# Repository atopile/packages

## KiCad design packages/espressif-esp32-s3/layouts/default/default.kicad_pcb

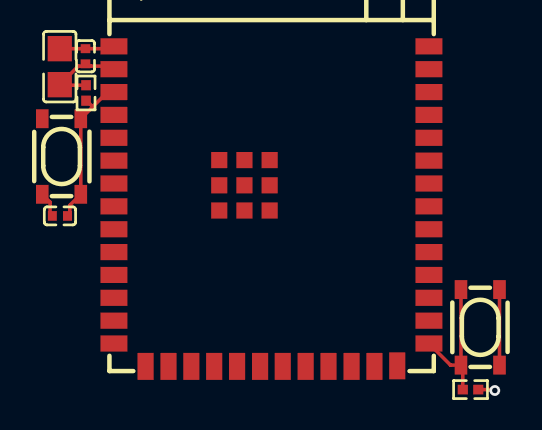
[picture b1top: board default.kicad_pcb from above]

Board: 2 copper layers, 8 parts (0 on the bottom side), 4 nets.

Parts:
C1: 10µF ±10%; C0805
C2: 100nF ±10%; C0402
C3: 1µF ±10%; C0402
R1, R2: 10kΩ ±1%; R0402
SW1, SW2: KEY-SMD_4P-L4.2-W3.2-P2.20-LS4.6
U1: WIRELM-SMD_ESP32-S3-WROOM-1

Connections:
c_en-power-hv: C3.1, R2.2, SW2.3, SW2.4, U1.3
hv: C1.1, C2.1, R1.1, R2.1, U1.2
lv: C1.2, C2.2, C3.2, SW1.1, SW1.2, SW2.1, SW2.2, U1.1, U1.40, U1.41
output: R1.2, SW1.3, SW1.4, U1.27

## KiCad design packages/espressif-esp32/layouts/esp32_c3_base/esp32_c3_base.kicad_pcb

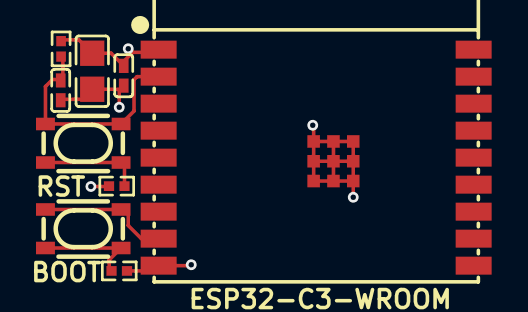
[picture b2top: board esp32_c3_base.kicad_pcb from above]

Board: 2 copper layers, 9 parts (0 on the bottom side), 6 nets.

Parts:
C1: 100nF ±10% 16V X7R; C0402
C2: 10µF ±10% 25V X5R; C0805
C3: 1µF ±10% 25V X5R; C0402
R1, R3: 100Ω ±1% 62.5mW; R0402
R2: 10kΩ ±1% 62.5mW; R0402
SW1, SW2: KEY-SMD_4P-L4.2-W3.2-P2.20-LS4.6
U1: BULETM-SMD_ESPRESSIF_ESP32-C3-WROOM-02-N4-4MB

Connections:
EN: C3.1, R2.1, SW2.1, SW2.2, U1.2
gnd: C1.2, C2.2, C3.2, R1.2, R3.2, U1.9, U1.19
hv: C1.1, C2.1, R2.2, U1.1
line: SW1.1, SW1.2, U1.8
unnamed[1]: R1.1, SW1.3, SW1.4
unnamed[1]-1: R3.1, SW2.3, SW2.4

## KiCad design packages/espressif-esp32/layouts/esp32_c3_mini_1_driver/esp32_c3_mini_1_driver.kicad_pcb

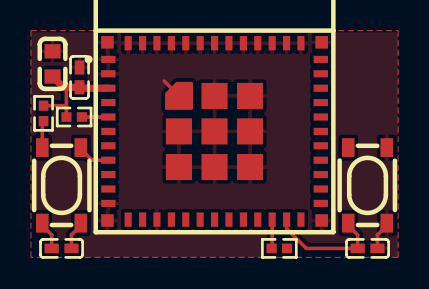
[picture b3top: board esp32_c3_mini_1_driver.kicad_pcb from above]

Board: 2 copper layers, 10 parts (0 on the bottom side), 7 nets.

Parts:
C1, C2, C4: 100nF ±10% 16V X7R; C0402
C3: 22µF ±20% 6.3V X5R; C0603
R1, R2, R3: 10kΩ ±1% 62.5mW; R0402
SW1, SW2: KEY-SMD_4P-L4.2-W3.2-P2.20-LS4.6
U1: WIFIM-SMD_ESP32-C3-MINI-1

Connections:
-line-0: R1.1, U1.5
-line-1: R2.1, U1.22
gnd: C1.1, C3.2, C4.2, SW1.1, SW1.2, U1.1, U1.2, U1.11, U1.14, U1.36, U1.37, U1.38, U1.39, U1.40, U1.41, U1.42, U1.43, U1.44, U1.45, U1.46, U1.47, U1.48, U1.49, U1.50, U1.51, U1.52, U1.53
hv: C3.1, C4.1, R1.2, R2.2, R3.2, U1.3
input: C2.1, R3.1, SW2.1, SW2.2
output-0: C1.2, SW1.3, SW1.4, U1.23
output-1: C2.2, SW2.3, SW2.4, U1.8

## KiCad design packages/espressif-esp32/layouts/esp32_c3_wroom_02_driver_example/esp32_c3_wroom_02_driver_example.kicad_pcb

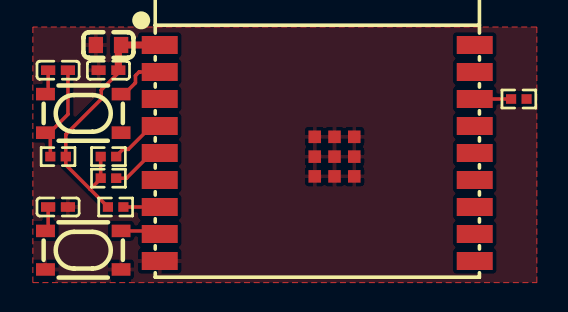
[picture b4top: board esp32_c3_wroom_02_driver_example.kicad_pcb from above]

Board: 2 copper layers, 12 parts (0 on the bottom side), 9 nets.

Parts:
C1, C2, C4: 100nF ±10% 16V X7R; C0402
C3: 22µF ±20% 6.3V X5R; C0603
R1, R2, R3, R4, R5: 10kΩ ±1% 62.5mW; R0402
SW1, SW2: KEY-SMD_4P-L4.2-W3.2-P2.20-LS4.6
U1: WIFIM-SMD_18P-L20.0-W18.0-P1.50

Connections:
-line-0: R5.2, U1.5
-line-1: R4.2, U1.4
-line-5: R2.1, U1.7
gnd: C1.1, C3.2, C4.2, SW1.1, SW1.2, U1.9, U1.19
hv: C3.1, C4.1, R1.2, R2.2, R3.2, R4.1, R5.1, U1.1
input: C2.1, R3.1, SW2.1, SW2.2
mcu-line: R1.1, U1.16
output-0: C1.2, SW1.3, SW1.4, U1.8
output-1: C2.2, SW2.3, SW2.4, U1.2

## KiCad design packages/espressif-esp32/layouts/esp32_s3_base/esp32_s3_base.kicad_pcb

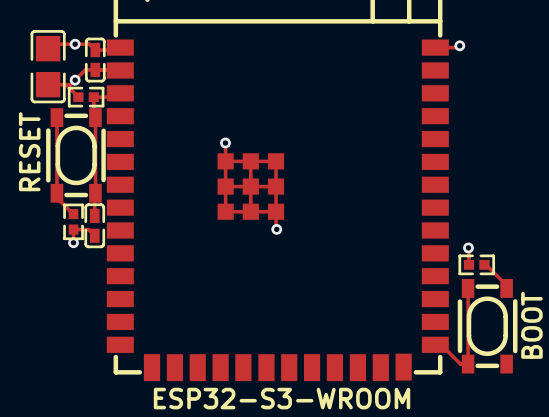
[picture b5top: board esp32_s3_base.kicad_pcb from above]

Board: 2 copper layers, 9 parts (0 on the bottom side), 6 nets.

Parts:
C1: 100nF ±10% 16V X7R; C0402
C2: 22µF ±20% 25V X5R; C0805
C3: 1µF ±10% 25V X5R; C0402
R1, R3: 100Ω ±1% 62.5mW; R0402
R2: 10kΩ ±1% 62.5mW; R0402
SW1, SW2: KEY-SMD_4P-L4.2-W3.2-P2.20-LS4.6
U1: WIRELM-SMD_ESP32-S3-WROOM-1

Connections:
EN: C3.1, R2.1, SW2.1, SW2.2, U1.3
gnd: C1.2, C2.2, C3.2, R1.2, R3.2, U1.1, U1.40, U1.41
hv: C1.1, C2.1, R2.2, U1.2
line: SW1.1, SW1.2, U1.27
unnamed[1]: R3.1, SW2.3, SW2.4
unnamed[1]-1: R1.1, SW1.3, SW1.4
